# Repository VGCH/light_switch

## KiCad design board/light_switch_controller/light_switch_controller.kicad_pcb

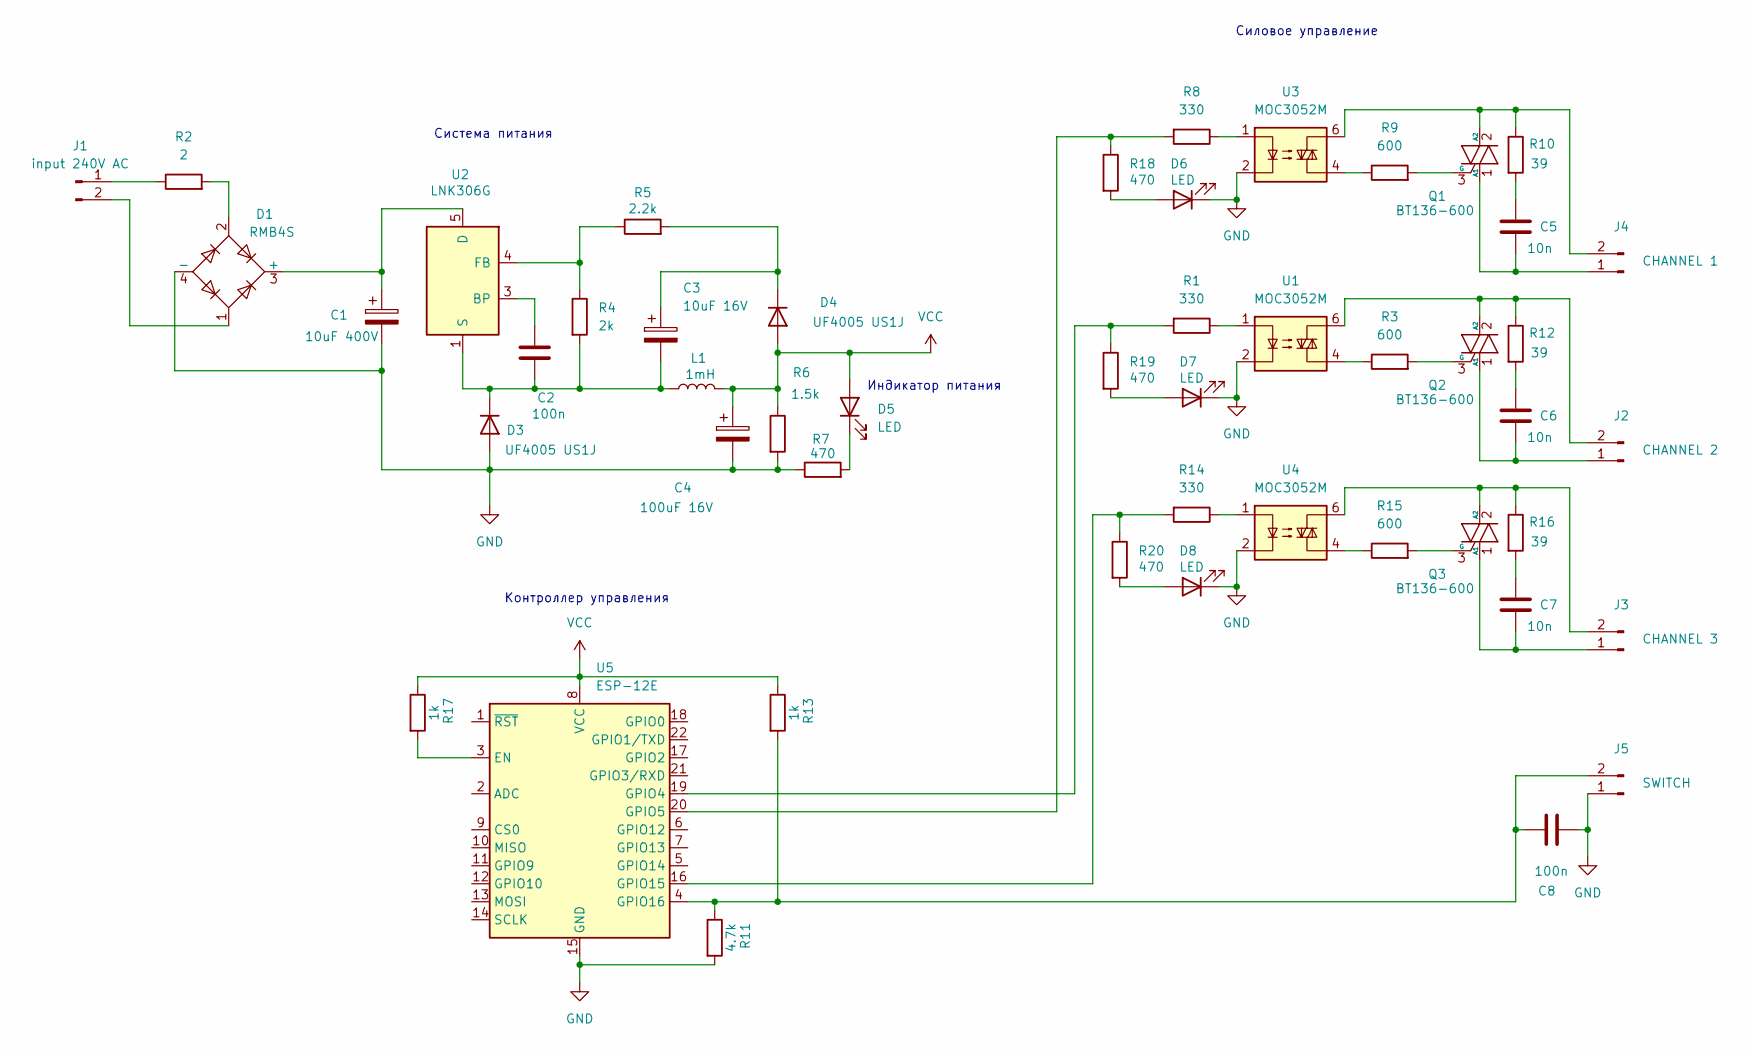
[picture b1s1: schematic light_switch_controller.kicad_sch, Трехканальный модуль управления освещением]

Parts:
C1: 10uF 400V; CP_Radial_D8.0mm_P3.80mm
C2, C8: 100n; C_1206_3216Metric
C3: 10uF 16V; CP_EIA-7343-31_Kemet-D_Pad2.25x2.55mm_HandSolder
C4: 100uF 16V; CP_EIA-7343-31_Kemet-D_Pad2.25x2.55mm_HandSolder
C5, C6, C7: 10n; C_1206_3216Metric
D1: RMB4S; TO-269AA
D3, D4: UF4005 US1J; D_MELF
D5, D6, D7, D8: LED; LED_1206_3216Metric
J1: input 240V AC; TerminalBlock_bornier-2_P5.08mm
J2: CHANNEL 2; TerminalBlock_bornier-2_P5.08mm
J3: CHANNEL 3; TerminalBlock_bornier-2_P5.08mm
J4: CHANNEL 1; TerminalBlock_bornier-2_P5.08mm
J5: SWITCH; TerminalBlock_bornier-2_P5.08mm
L1: 1mH; L_Taiyo-Yuden_NR-50xx
Q1, Q2, Q3: BT136-600; TO-252-2
R1, R8, R14: 330; R_0805_2012Metric
R2: 2; R_1206_3216Metric
R3, R9, R15: 600; R_0805_2012Metric
R4: 2k; R_0805_2012Metric
R5: 2.2k; R_0805_2012Metric
R6: 1.5k; R_0805_2012Metric
R7, R18, R19, R20: 470; R_0805_2012Metric
R10, R12, R16: 39; R_1206_3216Metric
R11: 4.7k; R_0805_2012Metric
R13, R17: 1k; R_0805_2012Metric
U1, U3, U4: MOC3052M; DIP-6_W7.62mm
U2: LNK306G; SOP-8_3.76x4.96mm_P1.27mm
U5: ESP-12E

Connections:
GND: C1.2, C4.2, C8.1, D1.4 (-), D3.2 (A), D6.1 (K), D7.1 (K), D8.1 (K), J5.1, R6.2, R7.1, R11.2, U1.2, U3.2, U4.2, U5.15 (GND)
unnamed: C5.1, R10.2
unnamed: C6.1, R12.2
unnamed: C7.1, R16.2
unnamed: C1.1, D1.3 (+), U2.5 (D)
unnamed: D1.2, R2.2
unnamed: C2.1, C3.2, D3.1 (K), L1.1, R4.2, U2.1 (S), U2.2 (S), U2.7 (S), U2.8 (S)
unnamed: C3.1, D4.1 (K), R5.2
unnamed: D5.1 (K), R7.2
unnamed: D6.2 (A), R18.2
unnamed: D7.2 (A), R19.2
unnamed: D8.2 (A), R20.2
unnamed: J1.1, R2.1
unnamed: D1.1, J1.2
unnamed: C6.2, J2.1, Q2.1 (A1)
unnamed: J2.2, Q2.2 (A2), R12.1, U1.6
unnamed: C7.2, J3.1, Q3.1 (A1)
unnamed: J3.2, Q3.2 (A2), R16.1, U4.6
unnamed: C5.2, J4.1, Q1.1 (A1)
unnamed: J4.2, Q1.2 (A2), R10.1, U3.6
unnamed: C8.2, J5.2, R11.1, R13.2, U5.4 (GPIO16)
unnamed: Q1.3 (G), R9.2
unnamed: Q2.3 (G), R3.2
unnamed: Q3.3 (G), R15.2
unnamed: R1.1, U1.1
unnamed: R3.1, U1.4
unnamed: R8.1, U3.1
unnamed: R9.1, U3.4
unnamed: R14.1, U4.1
unnamed: R15.1, U4.4
unnamed: C2.2, U2.3 (BP)
unnamed: R4.1, R5.1, U2.4 (FB)
unnamed: R17.2, U5.3 (EN)
unnamed: R1.2, R19.1, U5.19 (GPIO4)
unnamed: R8.2, R18.1, U5.20 (GPIO5)
unnamed: R14.2, R20.1, U5.16 (GPIO15)
VCC: C4.1, D4.2 (A), D5.2 (A), L1.2, R6.1, R13.1, R17.1, U5.8 (VCC)

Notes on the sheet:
Силовое управление
Система питания
Контроллер управления
Индикатор питания

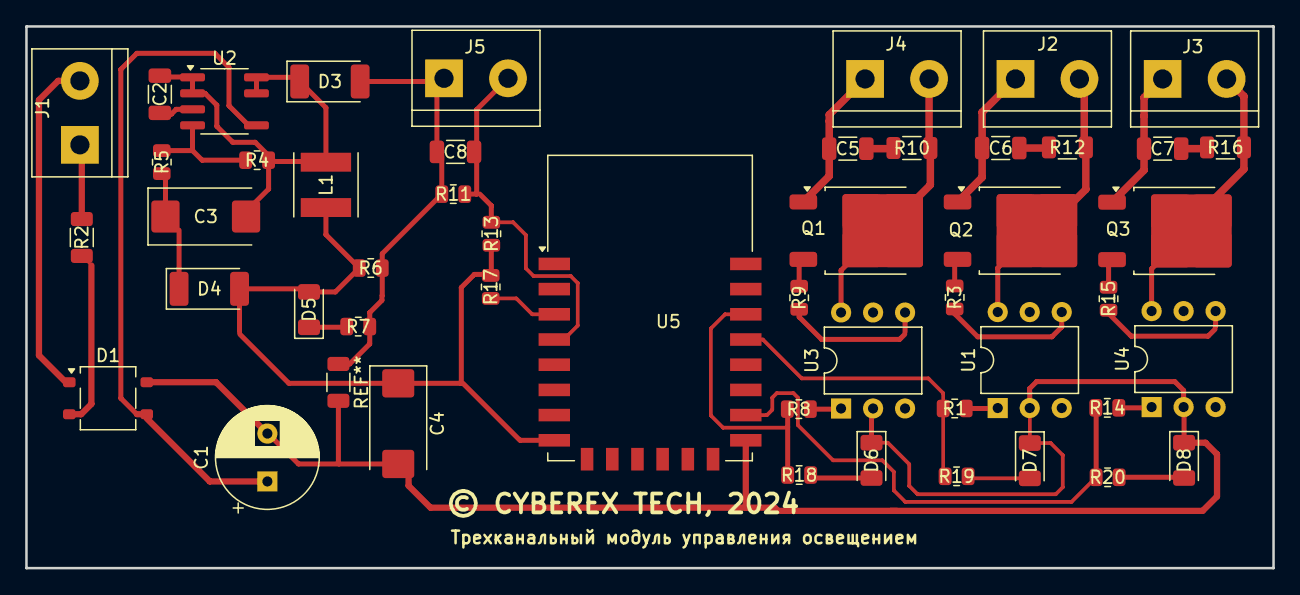
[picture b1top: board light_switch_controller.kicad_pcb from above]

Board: 2 copper layers, 99.0 x 43.0 mm, 49 parts (0 on the bottom side), 37 nets.

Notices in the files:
board/light_switch_controller/light_switch_controller.kicad_pcb:
© CYBEREX TECH, 2024
